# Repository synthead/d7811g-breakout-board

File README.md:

# Synthead D7811G Breakout Board

This little PCB helps you socket your D7811G CPU!  These are found in a lot of Roland and Casio synthesizers.

If you have socketed your D7811G to use the [KiwiTechnics Kiwi-106 CPU upgrade](https://www.kiwitechnics.com/kiwi-106.htm), this PCB offers a way to use the original CPU with the existing socket.

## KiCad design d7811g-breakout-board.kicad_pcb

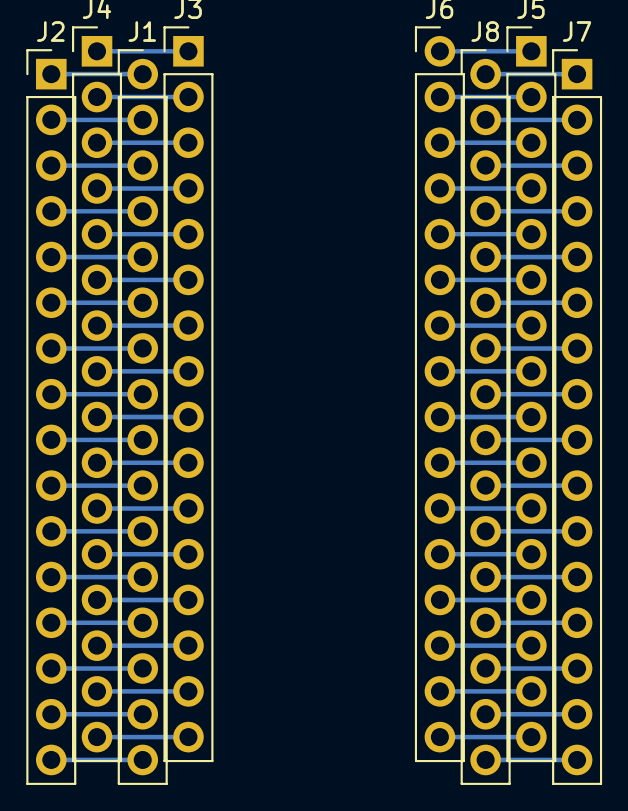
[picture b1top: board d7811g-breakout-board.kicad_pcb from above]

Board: 2 copper layers, 8 parts (0 on the bottom side), 64 nets.

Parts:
J1, J3, J5, J7: Conn_01x16_Male; PinHeader_1x16_P2.54mm_Vertical
J2, J4, J6, J8: Conn_01x16_Female; PinHeader_1x16_P2.54mm_Vertical

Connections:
unnamed: J1.1, J2.1
unnamed: J1.2, J2.2
unnamed: J1.3, J2.3
unnamed: J1.4, J2.4
unnamed: J1.5, J2.5
unnamed: J1.6, J2.6
unnamed: J1.7, J2.7
unnamed: J1.8, J2.8
unnamed: J1.9, J2.9
unnamed: J1.10, J2.10
unnamed: J1.11, J2.11
unnamed: J1.12, J2.12
unnamed: J1.13, J2.13
unnamed: J1.14, J2.14
unnamed: J1.15, J2.15
unnamed: J1.16, J2.16
unnamed: J3.1, J4.1
unnamed: J3.2, J4.2
unnamed: J3.3, J4.3
unnamed: J3.4, J4.4
unnamed: J3.5, J4.5
unnamed: J3.6, J4.6
unnamed: J3.7, J4.7
unnamed: J3.8, J4.8
unnamed: J3.9, J4.9
unnamed: J3.10, J4.10
unnamed: J3.11, J4.11
unnamed: J3.12, J4.12
unnamed: J3.13, J4.13
unnamed: J3.14, J4.14
unnamed: J3.15, J4.15
unnamed: J3.16, J4.16
unnamed: J5.1, J6.1
unnamed: J5.2, J6.2
unnamed: J5.3, J6.3
unnamed: J5.4, J6.4
unnamed: J5.5, J6.5
unnamed: J5.6, J6.6
unnamed: J5.7, J6.7
unnamed: J5.8, J6.8
unnamed: J5.9, J6.9
unnamed: J5.10, J6.10
unnamed: J5.11, J6.11
unnamed: J5.12, J6.12
unnamed: J5.13, J6.13
unnamed: J5.14, J6.14
unnamed: J5.15, J6.15
unnamed: J5.16, J6.16
unnamed: J7.1, J8.1
unnamed: J7.2, J8.2
unnamed: J7.3, J8.3
unnamed: J7.4, J8.4
unnamed: J7.5, J8.5
unnamed: J7.6, J8.6
unnamed: J7.7, J8.7
unnamed: J7.8, J8.8
unnamed: J7.9, J8.9
unnamed: J7.10, J8.10
unnamed: J7.11, J8.11
unnamed: J7.12, J8.12
unnamed: J7.13, J8.13
unnamed: J7.14, J8.14
unnamed: J7.15, J8.15
unnamed: J7.16, J8.16

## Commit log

2020-10-26 Initial commit. Include schematic, PCB, and render.
2020-10-26 Add README.md.
